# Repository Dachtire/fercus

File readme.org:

#+TITLE: Fercus
Wireless Symmetry Optical Keyboard[[./doc/image/overview.jpg]]

* Firmware
** Connect via RF 2.4GHz Proprietary, BLE 5.3, USB
** COMMENT optical switch with diff trigger mode
# - schmitt trigger
# - adc trigger
# - adc difference
** COMMENT function
# - multiple layers
# - repeat mode

* Hardware
** Switch
6*7 keys of each side, low profile optical switch
# - raesha low profile optical switch
# - keychron low profile optical switch
# - razer low profile optical switch

** Spec
Dimension: 133 * 137 * 14.35 mm

Weight of each side: 159 ± 1 g

power input: DC 5V 500mA

# current: 40 mA * 7 * 15 / 1000 = 4.2 mA

** response time
|    |       tr |       tf | unit |
| pt |       18 |        5 | us   |
# | sw | 200-2000 | 200-2000 | us   |
The speed of optical switch depends on the speed of finger, the shortest time for finger to press a switch is about 200 us, but usually it takes a few milliseconds.
Test on mcu's adc at f_adc = 12MHz, f_s = 12 / 14 MHz, resolution = 12 bits. Get the average of the five.

** COMMENT test
|    | min | typ | max | unit | cond                    |
| pt | 0.2 |     | 0.3 | V    | ir 20mA, without switch |

* Manual
** fn key
fn1: switch layout

fn2: switch connection mode. long press: rf Unbind with dongle

fn3: battery status

fn4: power on led green. power off led red.

** usb connection
- usb1 to connect with pc
#+begin_src org
              ┌────┐              
              │ pc │              
              └▲──▲┘              
               │  │               
    ┌───usb────┘  └────usb───┐    
    │                        │    
┌───▼──┬──────┐    ┌──────┬──▼───┐
│ usb1 │ usb2 │    │ usb2 │ usb1 │
├──────┴──────┤    ├──────┴──────┤
│    left     │    │    right    │
└─────────────┘    └─────────────┘
#+end_src
- usb2 to connect between left and right
#+begin_src org
              ┌────┐                                 ┌────┐              
              │ pc │                                 │ pc │              
              └▲───┘                                 └───▲┘              
               │                                         │               
    ┌───usb────┘                                         └────usb───┐    
    │                                                               │    
    │      ┌───usb────┐                           ┌───usb────┐      │    
    │      │          │                           │          │      │    
┌───▼──┬───▼──┐    ┌──▼───┬──────┐     ┌──────┬───▼──┐    ┌──▼───┬──▼───┐
│ usb1 │ usb2 │    │ usb2 │ usb1 │     │ usb1 │ usb2 │    │ usb2 │ usb1 │
├──────┴──────┤    ├──────┴──────┤     ├──────┴──────┤    ├──────┴──────┤
│    left     │    │    right    │     │    left     │    │    right    │
└─────────────┘    └─────────────┘     └─────────────┘    └─────────────┘
#+end_src

#               ┌────┐              
#               │ pc │              
#               └▲──▲┘              
#                │  │               
#     ┌───usb────┘  └────usb───┐    
#     │                        │    
#     │      ┌───usb────┐      │    
#     │      │          │      │    
# ┌───▼──┬───▼──┐    ┌──▼───┬──▼───┐
# │ usb1 │ usb2 │    │ usb2 │ usb1 │
# ├──────┴──────┤    ├──────┴──────┤
# │    left     │    │    right    │
# └─────────────┘    └─────────────┘

** RF connection
#+begin_src org
              ┌────┐              
              │ pc │              
              └─▲──┘              
                │usb              
             ┌──▼───┐             
  ┌─wireless─►dongle◄─wireless─┐  
  │          └──────┘          │  
  │                            │  
┌─▼───────────┐    ┌───────────▼─┐
│     RF      │    │     RF      │
├─────────────┤    ├─────────────┤
│    left     │    │    right    │
└─────────────┘    └─────────────┘
#+end_src

** BLE connection
#+begin_src org
              ┌────┐              
  ┌─wireless──► pc ◄──wireless─┐  
  │           └────┘           │  
  │                            │  
┌─▼───────────┐    ┌───────────▼─┐
│    BLE      │    │    BLE      │
├─────────────┤    ├─────────────┤
│    left     │    │    right    │
└─────────────┘    └─────────────┘
#+end_src

** mix connection
#+begin_src org
              ┌────┐              
              │ pc │              
              └▲───┘              
               │                  
    ┌───usb────┘                  
    │                             
    │      ┌─wireless─┐           
    │      │          │           
┌───▼──┬───▼──┐    ┌──▼───┬──────┐
│ usb1 │  RF  │    │  RF  │ usb1 │
├──────┴──────┤    ├──────┴──────┤
│    left     │    │    right    │
└─────────────┘    └─────────────┘
#+end_src

** power
auto power on/off when usb cable connected/disconnected

when idle for a week, first use fn4 to power off in firmware, then turn off hardware power switch

** layout
- qwerty[[./doc/keyboard-layout-editor/qwerty.png]]

* Assembly
** compoment
- pcb 1.6mm thickness
- plate 1.2mm thickness
- nut m2 length 2.5mm, od 3mm
- screw m2 length 4mm
- rubber 1mm thickness
- li-on battery 101550 800mAh, molex picoblade 3 pin, 8 cm cable length
- usb-c to usb-c cable 1 m
- usb-c to usb-a cable 2 m
  
** COMMENT PCBA
soldering nut on pcb, or soldering nut on plate

** Overall
1. Install switches on the plate, the LED position of the switch is facing upwards.
2. Install the plate to the PCB.[[./doc/image/assembly/assembly-1.jpg]]
3. Install the screws.[[./doc/image/assembly/assembly-2.jpg]]
4. Install keycaps.

* Thanks
[[https://discord.com/channels/715975244896272618][Optical Future Discord]]

* COMMENT FAQ
** COMMENT keys layout
*** thumb
finger splay increase the x axis distence between rows
more thumb keys may be hard to press
*** middle finger
[[./doc/keyboard-layout-editor/middle-finger.png]]
mid finger at wsad postion, non stagger is better to press up
bad for playing fps game
# same for pinky stagger 8 mm instand of 12 mm

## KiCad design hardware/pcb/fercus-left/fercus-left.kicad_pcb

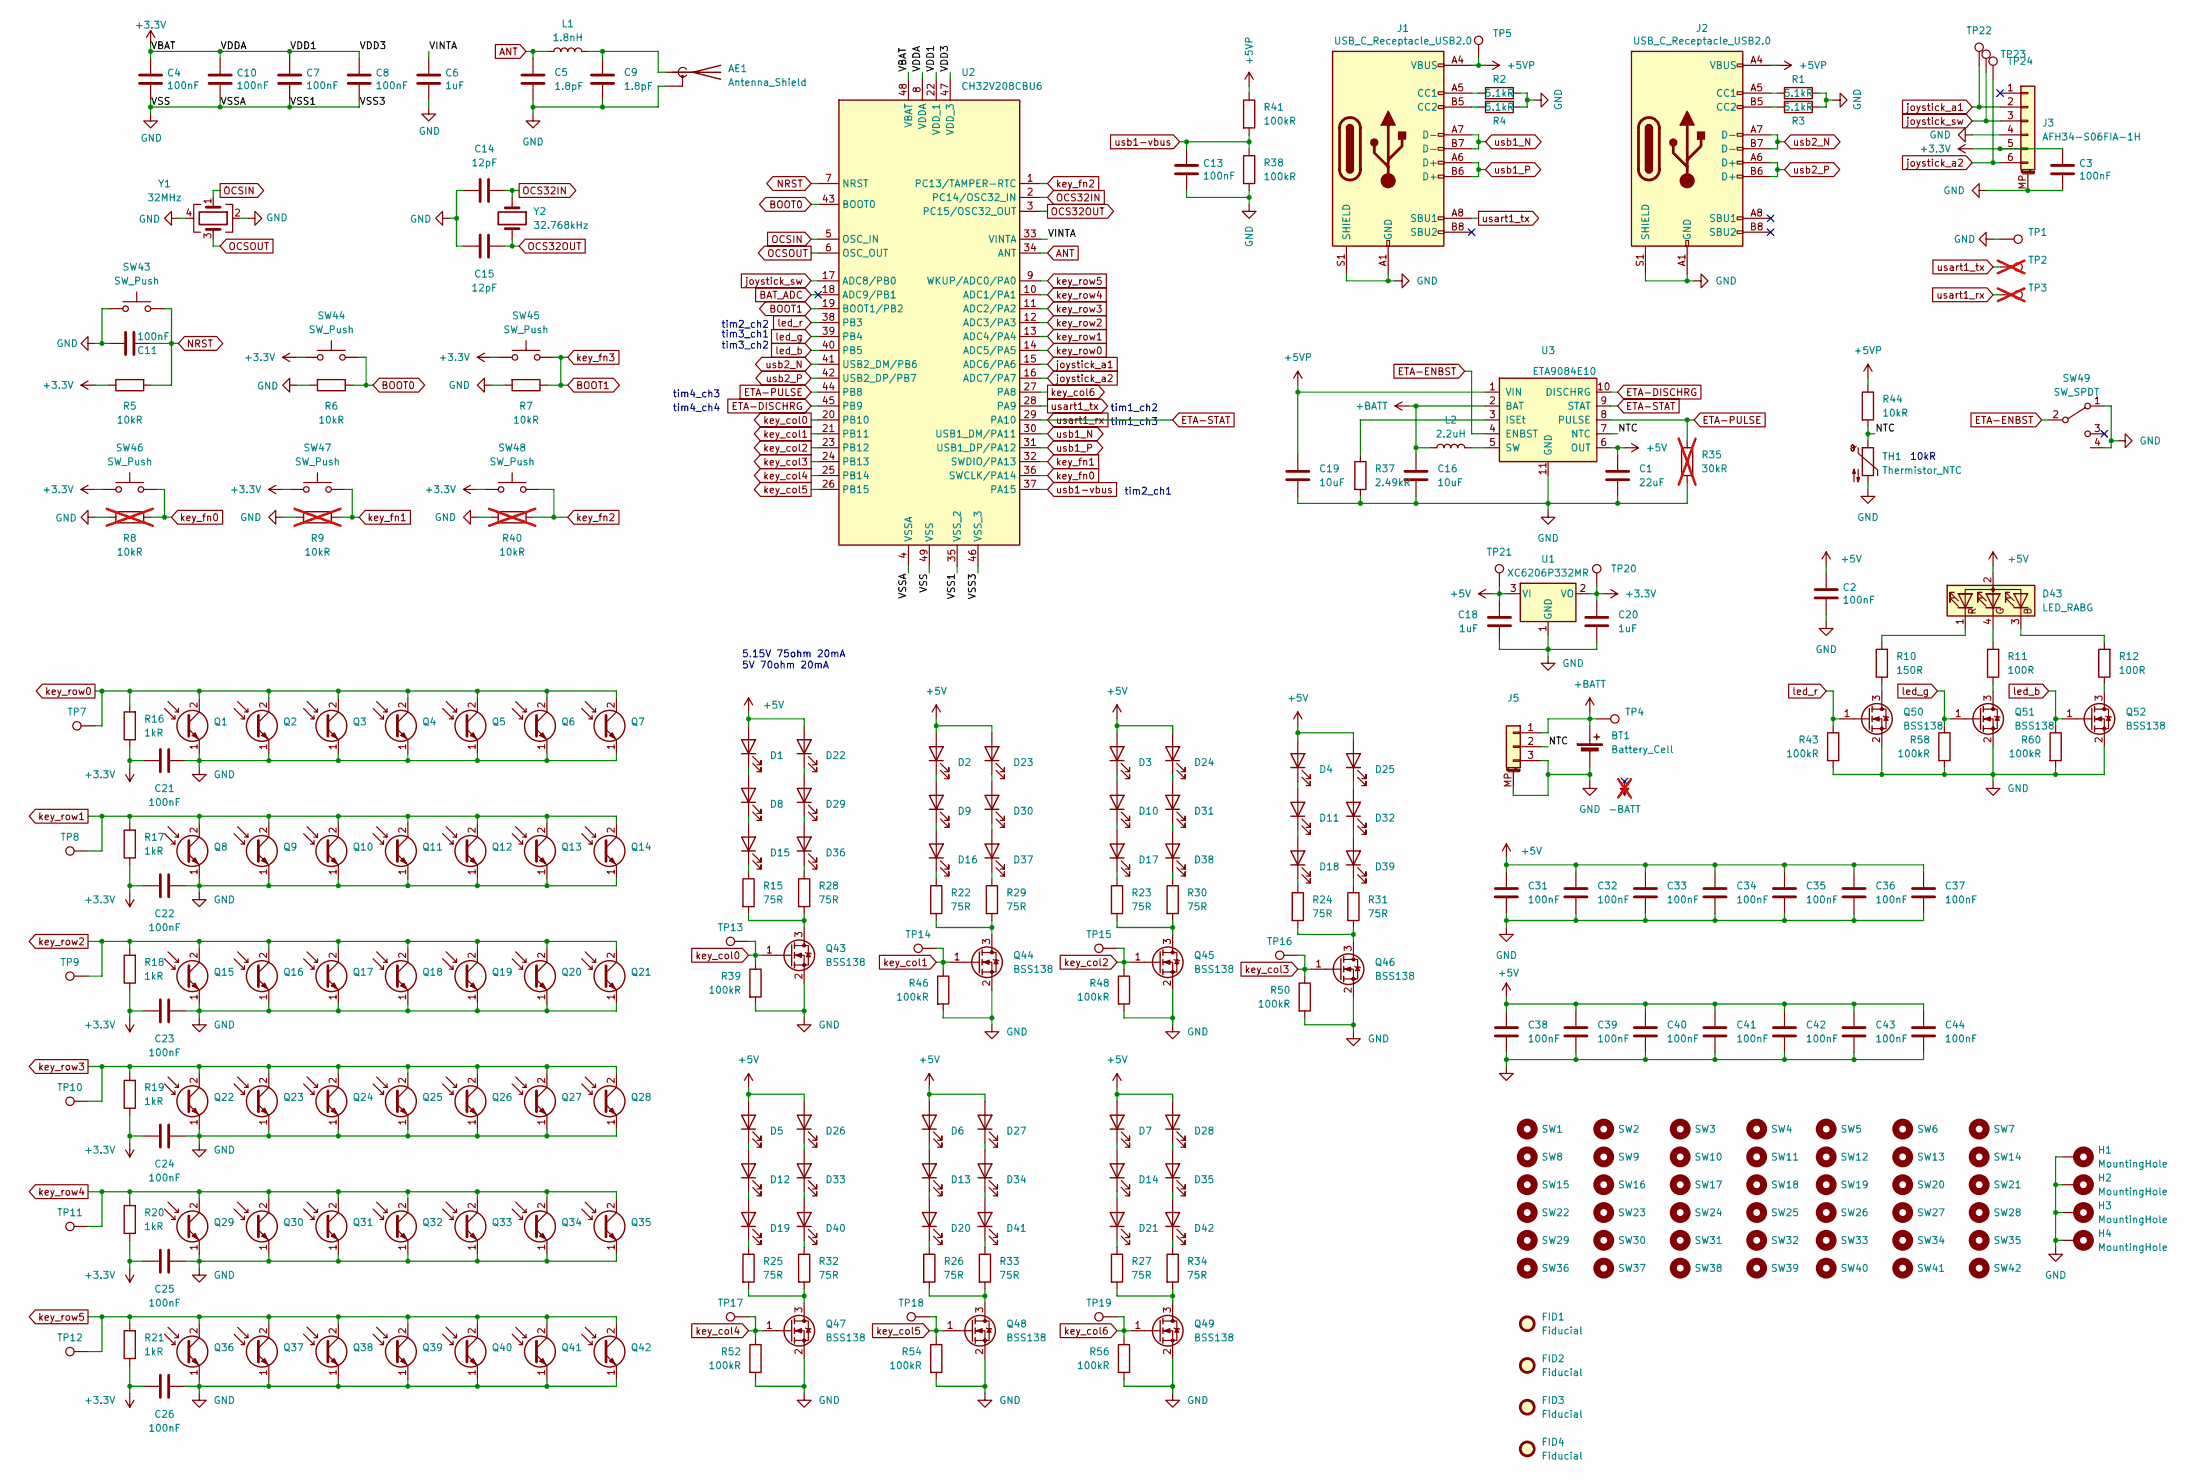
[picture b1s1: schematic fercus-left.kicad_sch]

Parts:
AE1: Antenna_Shield; WCH_MIFA-1_2.4G_1.6mm_FR4_Left_NoMask
BT1: Battery_Cell
C1: 22uF; C_0603_1608Metric
C2, C3, C4, C7, C8, C10, C11, C13, C21, C22, C23, C24, C25, C26, C31, C32, C33, C34, C35, C36, C37, C38, C39, C40, C41, C42, C43, C44: 100nF; C_0603_1608Metric
C5, C9: 1.8pF; C_0402_1005Metric
C6, C18, C20: 1uF; C_0603_1608Metric
C14, C15: 12pF; C_0402_1005Metric
C16: 10uF; C_0603_1608Metric
C19: 10uF; C_0805_2012Metric
D1, D2, D3, D4, D5, D6, D7, D8, D9, D10, D11, D12, D13, D14, D15, D16, D17, D18, D19, D20, D21, D22, D23, D24, D25, D26, D27, D28, D29, D30, D31, D32, D33, D34, D35, D36, D37, D38, D39, D40, D41, D42: KTR-0602IRC-850; KTR-0602IRC
D43: LED_RABG; Everlight_LED_RGB_PLCC-4
FID1, FID2, FID3, FID4: Fiducial; Fiducial_1mm_Mask3mm
H1, H2, H3, H4: MountingHole; MountingHole_2.2mm_M2_ISO14580_Pad
J1, J2: USB_C_Receptacle_USB2.0; USB_C_Receptacle_HRO_TYPE-C-31-M-12
J3: AFH34-S06FIA-1H; Jushuo_AFC42-S06FMA-1H_1x6-1MP_P0.50_Horizontal
J5: Molex_PicoBlade_53261-0371_1x03-1MP_P1.25mm_Horiz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; Molex_PicoBlade_53261-0371_1x03-1MP_P1.25mm_Horizontal
L1: 1.8nH; L_0402_1005Metric
L2: 2.2uH; L_Sunlord_MWSA0402S
Q1, Q2, Q3, Q4, Q5, Q6, Q7, Q8, Q9, Q10, Q11, Q12, Q13, Q14, Q15, Q16, Q17, Q18, Q19, Q20, Q21, Q22, Q23, Q24, Q25, Q26, Q27, Q28, Q29, Q30, Q31, Q32, Q33, Q34, Q35, Q36, Q37, Q38, Q39, Q40, Q41, Q42: KTR-0602PTD
Q43, Q44, Q45, Q46, Q47, Q48, Q49, Q50, Q51, Q52: BSS138; SOT-23
R1, R2, R3, R4: 5.1kR; R_0603_1608Metric
R5, R6, R7, R44: 10kR; R_0603_1608Metric
R8, R9, R40: 10kR; R_0603_1608Metric; not fitted
R10: 150R; R_0603_1608Metric
R11, R12: 100R; R_0603_1608Metric
R15, R22, R23, R24, R25, R26, R27, R28, R29, R30, R31, R32, R33, R34: 75R; R_0603_1608Metric
R16, R17, R18, R19, R20, R21: 1kR; R_0603_1608Metric
R35: 30kR; R_0603_1608Metric; not fitted
R37: 2.49kR; R_0402_1005Metric
R38, R39, R41, R43, R46, R48, R50, R52, R54, R56, R58, R60: 100kR; R_0603_1608Metric
SW1, SW2, SW3, SW4, SW5, SW6, SW7, SW8, SW9, SW10, SW11, SW12, SW13, SW14, SW15, SW16, SW17, SW18, SW19, SW20, SW21, SW22, SW23, SW24, SW25, SW26, SW27, SW28, SW29, SW30, SW31, SW32, SW33, SW34, SW35, SW36, SW37, SW38, SW39, SW40, SW41, SW42: SW_Optical; SW_RAESHA_Low_Profile_Optical
SW43, SW44, SW45, SW46, SW47, SW48: SW_Push; SW_SPST_TL3342
SW49: SW_SPDT; SW_SPDT_PCM12
TH1: Thermistor_NTC; R_0603_1608Metric
TP1, TP4, TP5, TP7, TP8, TP9, TP10, TP11, TP12, TP13, TP14, TP15, TP16, TP17, TP18, TP19, TP20, TP21, TP22, TP23, TP24: TestPoint; TestPoint_Pad_D1.0mm
TP2, TP3: TestPoint; TestPoint_Pad_D1.0mm; not fitted
U1: XC6206P332MR; SOT-23-3
U2: CH32V208CBU6; QFN-48-1EP_5x5mm_P0.35mm_EP3.7x3.7mm_ThermalVias_Drill0.3mm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
U3: ETA9084E10; SSOP-10-1EP_3.9x4.9mm_P1.00mm_EP2.4x2.8mm_ThermalVias_Drill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
Y1: 32MHz; Crystal_SMD_3225-4Pin_3.2x2.5mm
Y2: 32.768kHz; Crystal_SMD_3215-2Pin_3.2x1.5mm

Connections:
+3.3V: C3.1, C4.1, C7.1, C8.1, C10.1, C20.1, C21.1, C22.1, C23.1, C24.1, C25.1, C26.1, J3.5, R5.1, R16.1, R17.1, R18.1, R19.1, R20.1, R21.1, SW44.1, SW45.1, SW46.1, SW47.1, SW48.1, TP20.1, U1.2 (VO), U2.8 (VDDA), U2.22 (VDD_1), U2.47 (VDD_3), U2.48 (VBAT)
+5V: C1.1, C2.1, C18.1, C31.2, C32.2, C33.2, C34.2, C35.2, C36.2, C37.2, C38.2, C39.2, C40.2, C41.2, C42.2, C43.2, C44.2, D1.2 (A), D2.2 (A), D3.2 (A), D4.2 (A), D5.2 (A), D6.2 (A), D7.2 (A), D22.2 (A), D23.2 (A), D24.2 (A), D25.2 (A), D26.2 (A), D27.2 (A), D28.2 (A), D43.2 (A), TP21.1, U1.3 (VI), U3.6 (OUT)
+5VP: C19.1, J1.A4 (VBUS), J1.A9 (VBUS), J1.B4 (VBUS), J1.B9 (VBUS), J2.A4 (VBUS), J2.A9 (VBUS), J2.B4 (VBUS), J2.B9 (VBUS), R41.1, R44.1, TP5.1, U3.1 (VIN)
+BATT: BT1.1 (+), C16.1, J5.1, L2.1, TP4.1, U3.2 (BAT)
/NTC: J5.2, R44.2, TH1.1, U3.7 (NTC)
/VINTA: C6.1, U2.33 (VINTA)
ANT: C5.1, L1.1, U2.34 (ANT)
BAT_ADC: U2.18 (ADC9/PB1)
BOOT0: R6.1, SW44.2, U2.43 (BOOT0)
BOOT1: R7.1, SW45.2, U2.19 (BOOT1/PB2)
ETA-DISCHRG: U2.45 (PB9), U3.10 (DISCHRG)
ETA-ENBST: SW49.2 (B), U3.4 (ENBST)
ETA-PULSE: R35.1, U2.44 (PB8), U3.8 (PULSE)
ETA-STAT: TP3.1, U2.29 (PA10), U3.9 (STAT)
GND: AE1.2 (Shield), BT1.2 (-), C1.2, C2.2, C3.2, C4.2, C5.2, C6.2, C7.2, C8.2, C9.2, C10.2, C11.2, C13.2, C14.2, C15.2, C16.2, C18.2, C19.2, C20.2, C21.2, C22.2, C23.2, C24.2, C25.2, C26.2, C31.1, C32.1, C33.1, C34.1, C35.1, C36.1, C37.1, C38.1, C39.1, C40.1, C41.1, C42.1, C43.1, C44.1, H1.1, H2.1, H3.1, H4.1, J1.A1 (GND), J1.A12 (GND), J1.B1 (GND), J1.B12 (GND), J1.S1 (SHIELD), J2.A1 (GND), J2.A12 (GND), J2.B1 (GND), J2.B12 (GND), J2.S1 (SHIELD), J3.4, J3.MP (MountPin), J5.3, J5.MP (MountPin), Q1.1 (E), Q2.1 (E), Q3.1 (E), Q4.1 (E), Q5.1 (E), Q6.1 (E), Q7.1 (E), Q8.1 (E), Q9.1 (E), Q10.1 (E), Q11.1 (E), Q12.1 (E), Q13.1 (E), Q14.1 (E), Q15.1 (E), Q16.1 (E), Q17.1 (E), Q18.1 (E), Q19.1 (E), Q20.1 (E), Q21.1 (E), Q22.1 (E), Q23.1 (E), Q24.1 (E), Q25.1 (E), Q26.1 (E), Q27.1 (E), Q28.1 (E), Q29.1 (E), Q30.1 (E), Q31.1 (E), Q32.1 (E), Q33.1 (E), Q34.1 (E), Q35.1 (E), Q36.1 (E), Q37.1 (E), Q38.1 (E), Q39.1 (E), Q40.1 (E), Q41.1 (E), Q42.1 (E), Q43.2 (S), Q44.2 (S), Q45.2 (S), Q46.2 (S), Q47.2 (S), Q48.2 (S), Q49.2 (S), Q50.2 (S), Q51.2 (S), Q52.2 (S), R1.1, R2.1, R3.1, R4.1, R6.2, R7.2, R8.2, R9.2, R35.2, R37.2, R38.2, R39.2, R40.2, R43.2, R46.2, R48.2, R50.2, R52.2, R54.2, R56.2, R58.2, R60.2, SW43.1, SW49.1 (A), SW49.4, TH1.2, TP1.1, U1.1 (GND), U2.4 (VSSA), U2.35 (VSS_2), U2.46 (VSS_3), U2.49 (VSS), U3.11 (GND), Y1.2, Y1.4
NRST: C11.1, R5.2, SW43.2, U2.7 (NRST)
unnamed: AE1.1 (A), C9.1, L1.2
unnamed: D1.1 (K), D8.2 (A)
unnamed: D2.1 (K), D9.2 (A)
unnamed: D3.1 (K), D10.2 (A)
unnamed: D10.1 (K), D17.2 (A)
unnamed: D4.1 (K), D11.2 (A)
unnamed: D11.1 (K), D18.2 (A)
unnamed: D5.1 (K), D12.2 (A)
unnamed: D12.1 (K), D19.2 (A)
unnamed: D6.1 (K), D13.2 (A)
unnamed: D13.1 (K), D20.2 (A)
unnamed: D7.1 (K), D14.2 (A)
unnamed: D14.1 (K), D21.2 (A)
unnamed: D8.1 (K), D15.2 (A)
unnamed: D15.1 (K), R15.1
unnamed: D9.1 (K), D16.2 (A)
unnamed: D16.1 (K), R22.1
unnamed: D17.1 (K), R23.1
unnamed: D18.1 (K), R24.1
unnamed: D19.1 (K), R25.1
unnamed: D20.1 (K), R26.1
unnamed: D21.1 (K), R27.1
unnamed: D22.1 (K), D29.2 (A)
unnamed: D23.1 (K), D30.2 (A)
unnamed: D24.1 (K), D31.2 (A)
unnamed: D25.1 (K), D32.2 (A)
unnamed: D26.1 (K), D33.2 (A)
unnamed: D27.1 (K), D34.2 (A)
unnamed: D28.1 (K), D35.2 (A)
unnamed: D29.1 (K), D36.2 (A)
unnamed: D30.1 (K), D37.2 (A)
unnamed: D31.1 (K), D38.2 (A)
unnamed: D32.1 (K), D39.2 (A)
unnamed: D33.1 (K), D40.2 (A)
unnamed: D34.1 (K), D41.2 (A)
unnamed: D35.1 (K), D42.2 (A)
unnamed: D36.1 (K), R28.1
unnamed: D37.1 (K), R29.1
unnamed: D38.1 (K), R30.1
unnamed: D39.1 (K), R31.1
unnamed: D40.1 (K), R32.1
unnamed: D41.1 (K), R33.1
unnamed: D42.1 (K), R34.1
unnamed: D43.3 (BK), R12.2
unnamed: D43.4 (GK), R11.2
unnamed: D43.1 (RK), R10.2
unnamed: J1.A5 (CC1), R2.2
unnamed: J1.B5 (CC2), R4.2
unnamed: J2.A5 (CC1), R1.2
unnamed: J2.B5 (CC2), R3.2
unnamed: Q43.3 (D), R15.2, R28.2
unnamed: Q44.3 (D), R22.2, R29.2
unnamed: Q45.3 (D), R23.2, R30.2
unnamed: Q46.3 (D), R24.2, R31.2
unnamed: Q47.3 (D), R25.2, R32.2
unnamed: Q48.3 (D), R26.2, R33.2
unnamed: Q49.3 (D), R27.2, R34.2
unnamed: Q50.3 (D), R10.1
unnamed: Q51.3 (D), R11.1
unnamed: Q52.3 (D), R12.1
unnamed: R37.1, U3.3 (ISEt)
unnamed: L2.2, U3.5 (SW)
OCS32IN: C14.1, U2.2 (PC14/OSC32_IN), Y2.1
OCS32OUT: C15.1, U2.3 (PC15/OSC32_OUT), Y2.2
OCSIN: U2.5 (OSC_IN), Y1.1
OCSOUT: U2.6 (OSC_OUT), Y1.3
joystick_a1: J3.2, TP22.1, U2.15 (ADC6/PA6)
joystick_a2: J3.6, TP24.1, U2.16 (ADC7/PA7)
joystick_sw: J3.3, TP23.1, U2.17 (ADC8/PB0)
key_col0: Q43.1 (G), R39.1, TP13.1, U2.20 (PB10)
key_col1: Q44.1 (G), R46.1, TP14.1, U2.21 (PB11)
key_col2: Q45.1 (G), R48.1, TP15.1, U2.23 (PB12)
key_col3: Q46.1 (G), R50.1, TP16.1, U2.24 (PB13)
key_col4: Q47.1 (G), R52.1, TP17.1, U2.25 (PB14)
key_col5: Q48.1 (G), R54.1, TP18.1, U2.26 (PB15)
key_col6: Q49.1 (G), R56.1, TP19.1, U2.27 (PA8)
key_fn0: R8.1, SW46.2, U2.36 (SWCLK/PA14)
key_fn1: R9.1, SW47.2, U2.32 (SWDIO/PA13)
key_fn2: R40.1, SW48.2, U2.1 (PC13/TAMPER-RTC)
key_row0: Q1.2 (C), Q2.2 (C), Q3.2 (C), Q4.2 (C), Q5.2 (C), Q6.2 (C), Q7.2 (C), R16.2, TP7.1, U2.14 (ADC5/PA5)
key_row1: Q8.2 (C), Q9.2 (C), Q10.2 (C), Q11.2 (C), Q12.2 (C), Q13.2 (C), Q14.2 (C), R17.2, TP8.1, U2.13 (ADC4/PA4)
key_row2: Q15.2 (C), Q16.2 (C), Q17.2 (C), Q18.2 (C), Q19.2 (C), Q20.2 (C), Q21.2 (C), R18.2, TP9.1, U2.12 (ADC3/PA3)
key_row3: Q22.2 (C), Q23.2 (C), Q24.2 (C), Q25.2 (C), Q26.2 (C), Q27.2 (C), Q28.2 (C), R19.2, TP10.1, U2.11 (ADC2/PA2)
key_row4: Q29.2 (C), Q30.2 (C), Q31.2 (C), Q32.2 (C), Q33.2 (C), Q34.2 (C), Q35.2 (C), R20.2, TP11.1, U2.10 (ADC1/PA1)
key_row5: Q36.2 (C), Q37.2 (C), Q38.2 (C), Q39.2 (C), Q40.2 (C), Q41.2 (C), Q42.2 (C), R21.2, TP12.1, U2.9 (WKUP/ADC0/PA0)
led_b: Q52.1 (G), R60.1, U2.40 (PB5)
led_g: Q51.1 (G), R58.1, U2.39 (PB4)
led_r: Q50.1 (G), R43.1, U2.38 (PB3)
usart1_tx: J1.A8 (SBU1), TP2.1, U2.28 (PA9)
usb1-vbus: C13.1, R38.1, R41.2, U2.37 (PA15)
usb1_N: J1.A7 (D-), J1.B7 (D-), U2.30 (USB1_DM/PA11)
usb1_P: J1.A6 (D+), J1.B6 (D+), U2.31 (USB1_DP/PA12)
usb2_N: J2.A7 (D-), J2.B7 (D-), U2.41 (USB2_DM/PB6)
usb2_P: J2.A6 (D+), J2.B6 (D+), U2.42 (USB2_DP/PB7)

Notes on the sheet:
tim4_ch4
tim1_ch3
tim2_ch2
10kR
5.15V 75ohm 20mA 5V 70ohm 20mA
tim2_ch1
tim4_ch3
tim1_ch2
tim3_ch2
tim3_ch1

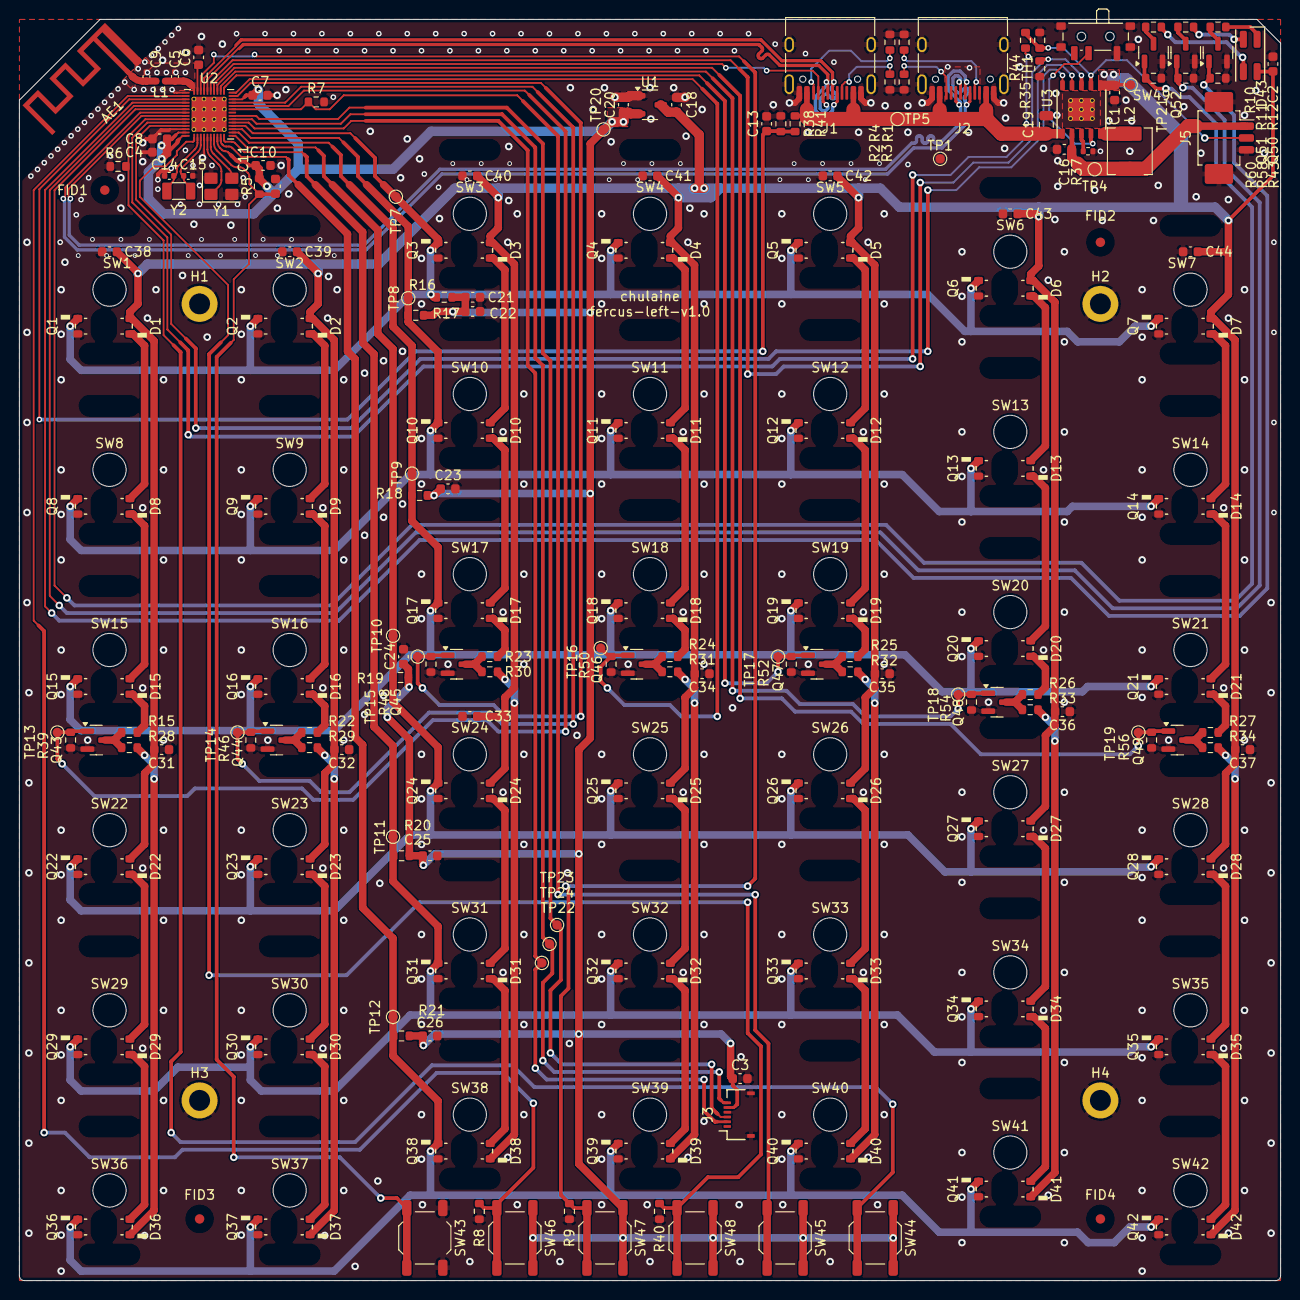
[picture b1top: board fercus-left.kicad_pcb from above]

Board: 2 copper layers, 133.0 x 133.0 mm, 272 parts (0 on the bottom side), 109 nets.

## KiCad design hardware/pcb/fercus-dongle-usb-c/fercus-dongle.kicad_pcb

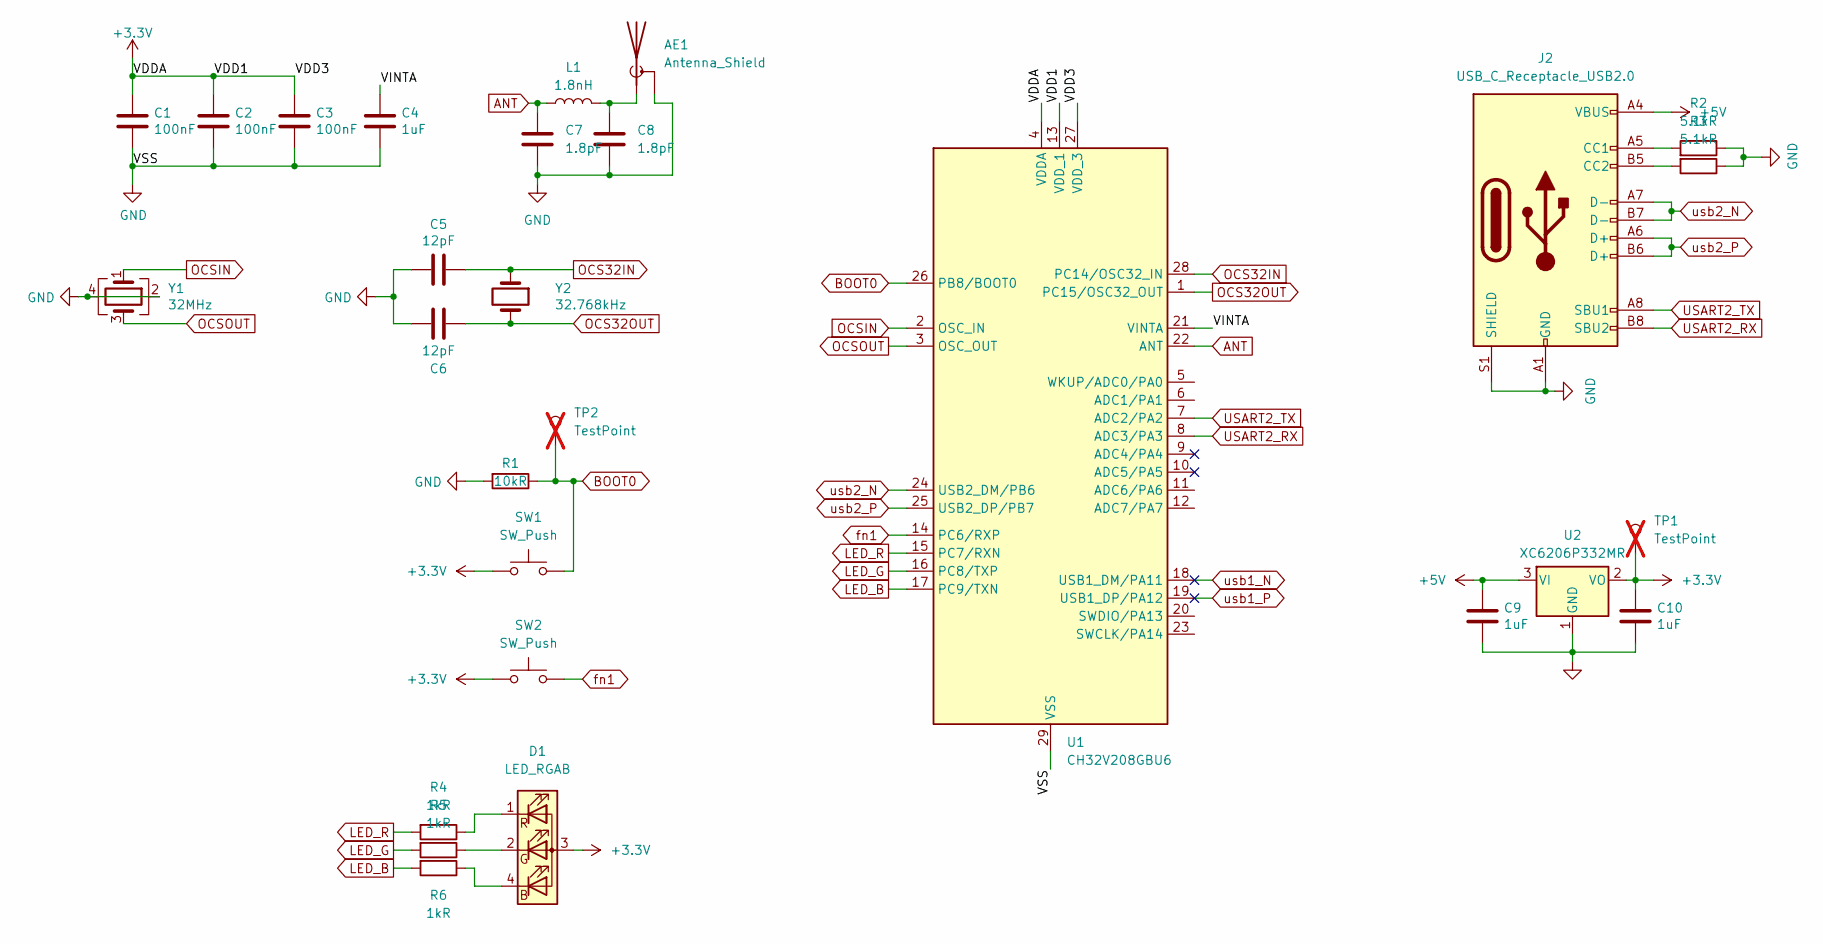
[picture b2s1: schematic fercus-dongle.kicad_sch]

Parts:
AE1: Antenna_Shield; WCH_MIFA-1_2.4GHz_1.6mm_FR4_Left_Mask
C1, C2, C3: 100nF; C_0402_1005Metric
C4, C9, C10: 1uF; C_0402_1005Metric
C5, C6: 12pF; C_0402_1005Metric
C7, C8: 1.8pF; C_0402_1005Metric
D1: LED_RGAB; KTR-B1615RGBC+
J2: USB_C_Receptacle_USB2.0; USB_C_Receptacle_HRO_TYPE-C-31-M-12
L1: 1.8nH; L_0402_1005Metric
R1: 10kR; R_0402_1005Metric
R2, R3: 5.1kR; R_0402_1005Metric
R4, R5, R6: 1kR; R_0402_1005Metric
SW1, SW2: SW_Push; SW_SPST_CK_KXT3
TP1, TP2: TestPoint; TestPoint_Pad_D1.0mm; not fitted
U1: CH32V208GBU6; QFN-28-1EP_4x4mm_P0.4mm_EP2.6x2.6mm_ThermalVias_Drill0.3mm
U2: XC6206P332MR; SOT-23
Y1: 32MHz; Crystal_SMD_2016-4Pin_2.0x1.6mm
Y2: 32.768kHz; Crystal_SMD_2012-2Pin_2.0x1.2mm

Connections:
+3.3V: C1.1, C2.1, C3.1, C10.1, D1.3 (A), SW1.1, SW2.1, TP1.1, U1.4 (VDDA), U1.13 (VDD_1), U1.27 (VDD_3), U2.2 (VO)
+5V: C9.1, J2.A4 (VBUS), J2.A9 (VBUS), J2.B4 (VBUS), J2.B9 (VBUS), U2.3 (VI)
/VINTA: C4.1, U1.21 (VINTA)
ANT: C7.1, L1.1, U1.22 (ANT)
BOOT0: R1.1, SW1.2, TP2.1, U1.26 (PB8/BOOT0)
GND: AE1.2 (Shield), C1.2, C2.2, C3.2, C4.2, C5.2, C6.2, C7.2, C8.2, C9.2, C10.2, J2.A1 (GND), J2.A12 (GND), J2.B1 (GND), J2.B12 (GND), J2.S1 (SHIELD), R1.2, R2.1, R3.1, U1.29 (VSS), U2.1 (GND), Y1.2, Y1.4
LED_B: R6.2, U1.17 (PC9/TXN)
LED_G: R5.2, U1.16 (PC8/TXP)
LED_R: R4.2, U1.15 (PC7/RXN)
unnamed: AE1.1 (A), C8.1, L1.2
unnamed: D1.4 (BK), R6.1
unnamed: D1.2 (GK), R5.1
unnamed: D1.1 (RK), R4.1
unnamed: J2.A5 (CC1), R2.2
unnamed: J2.B5 (CC2), R3.2
OCS32IN: C5.1, U1.28 (PC14/OSC32_IN), Y2.1
OCS32OUT: C6.1, U1.1 (PC15/OSC32_OUT), Y2.2
OCSIN: U1.2 (OSC_IN), Y1.1
OCSOUT: U1.3 (OSC_OUT), Y1.3
USART2_RX: J2.B8 (SBU2), U1.8 (ADC3/PA3)
USART2_TX: J2.A8 (SBU1), U1.7 (ADC2/PA2)
fn1: SW2.2, U1.14 (PC6/RXP)
usb1_N: U1.18 (USB1_DM/PA11)
usb1_P: U1.19 (USB1_DP/PA12)
usb2_N: J2.A7 (D-), J2.B7 (D-), U1.24 (USB2_DM/PB6)
usb2_P: J2.A6 (D+), J2.B6 (D+), U1.25 (USB2_DP/PB7)

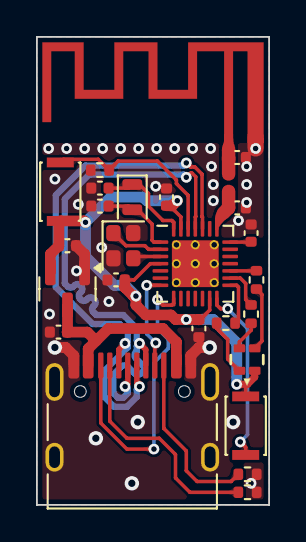
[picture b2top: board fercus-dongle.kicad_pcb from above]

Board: 2 copper layers, 12.9 x 26.0 mm, 26 parts (0 on the bottom side), 24 nets.

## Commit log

2022-07-23 v0.3.0
    add (firmware):
    system: 24Mhz HXTAL for 96Mhz system clock
    usb: hid keyborad
    feat (keyboard):
    uart dma communication
    multiple layers
2022-12-14 doc: add readme, license, image
2022-12-14 fw/ch32v: disable DEBUG_UART1
2022-12-14 fw/ch32v/usbd: add ONE_DESCRIPTOR
2022-12-14 fw/ch32v/usbd: add ENDP_ADDR
2022-12-14 fw/gd32v/usbfs: add device class, config
2022-12-14 fw/gd32v/usbfs: add usb hid define, usage
2022-12-14 fw: add keyboard
2022-12-14 fw/ch32v: rename usbd_composite_km to app
2022-12-14 fw/ch32v/usbd: merge 'v1.6' CH32V20xEVT/EXAM/USB/USBD/CompositeKM/User/USBLIB
    rename USBLIB to usbd
    rename CONFIG to config
    rename USB-Driver to driver
2022-12-14 fw/ch32v: add keyboard init to main()
2022-12-14 fw/ch32v: add define HSE_VALUE 24Mhz
2022-12-14 fw/gd32v/usbfs: merge GD32VF103_Firmware_Library_V1.1.4/Firmware/GD32VF103_usbfs_library/driver/Include
2022-12-14 fw/ch32v: add gpio_config(), USART1_Init(), TIM1_Init(), DMA_Tx_Init(), ADC_Function_Init(), USB_Sleep_Wakeup_CFG()
2022-12-14 fw/ch32v/usbd: add ENDP_SIZE
2022-12-14 fw/ch32v: add TIM1_UP_IRQHandler()
2022-12-14 fw/gd32v/usbfs: merge GD32VF103_Firmware_Library_V1.1.4/Firmware/GD32VF103_usbfs_library/ustd/common
2022-12-14 fw/ch32v/usbd: add EP1_OUT_Callback(), EP2_OUT_Callback()
2022-12-14 fw/ch32v: add 24Mhz HSE in SetSysClockTo144_HSE()
2022-12-14 fw/gd32v/usbfs: add USB_CLASS_VENDOR
2022-12-14 fw/makefile: add
2022-12-14 fw/ch32v: merge 'v1.6' CH32V20xEVT/EXAM/USB/USBD/CompositeKM/User
2022-12-14 fw/ch32v: merge 'v1.6' CH32V20xEVT/EXAM/SRC
2022-12-14 hw/pcb: add
2022-12-14 hw/case: add
2022-12-14 fw/gd32v/usbfs: merge GD32VF103_Firmware_Library_V1.1.4/Firmware/GD32VF103_usbfs_library/ustd/class/hid
    rename GD32VF103_usbfs_library to usbfs
2022-12-14 fw/ch32v: remove duplicate TIM3_Init(), TIM3_IRQHandler()
2022-12-14 fw/ch32v/usbfs: merge 'v1.6' CH32V20xEVT/EXAM/USB/USBFS/HOST_KM/User/USB_Host
2022-12-14 hw/plate: add
2022-12-14 fw: change gpio pin
2022-12-14 fw/ch32v/usbfs: remove duplicate USBFS_RCC_Init()
2022-12-14 fw/ch32v/usbfs: merge 'v1.6' CH32V20xEVT/EXAM/USB/USBFS/DEVICE/CompositeKM/User
2022-12-14 fw: add keyboard adc diff mode
    rename kb_adc_init() in keyboard.c to adc_config() in app.c
2022-12-14 fw: add kb_adc_time()
2022-12-14 hw/case: add joystick
2022-12-14 fw: add kb_adc_test3()
2022-12-14 Revert "fw/ch32v: disable DEBUG_UART1"
    This reverts commit 79287d2343aa877df28748973e31bd921e492df9.
2022-12-14 fw: add keyboard adc trigger mode
2022-12-14 fw/ch32v: add rcc adc clock
2022-12-14 fw: remove kb_adc_test()
2022-12-14 fw/usbfs: add usb host hid keyboard
    add usbh_epin_time() from TIM3_IRQHandler(), replace TIM3 with TIM1
2022-12-14 fw/ch32v: add usbh init to main()
2022-12-14 fw/ch32v: add usbfs host data handle, usbfs host init to main()
2022-12-14 fw/ch32v/usbfs: add include
2022-12-14 fw: remove printf in kb_usbhd_combine()
2022-12-14 hw/pcb: remove led
2022-12-14 doc: fix readme style
2022-12-15 doc/image: update overview
2022-12-15 hw/plate: remove led
2022-12-15 hw: change joystick mounting hole d
2022-12-15 fw/gd32v/usbfs: rename cntlr desc
2022-12-15 fw/gd32v/usbfs: rename paraments of usb_hid_desc_config_set
2022-12-15 fw/js: add gpio define, init, adc dma
2022-12-15 fw: fix define array size
2022-12-15 fw/ch32v/usbd: add USBD_COMPOSITE ONE_DESCRIPTOR
2022-12-15 fw/gd32v/usbfs: fix usbd_composite class
2022-12-16 doc: update usb connection
2022-12-16 fw/gd32v/usbfs: add usbd_cntlr_report_send()
2022-12-20 fw: fix cntlr handler
2022-12-20 doc: update time desc
2022-12-20 fw: fix kb handler
2022-12-28 fw: fix define
2022-12-28 fw: fix usb_prop
2024-04-20 init
    hw: add
    fw: add
    doc: add
2024-06-08 merge
    fw:
    - fix usb product string, vid
    - add rf_phy_hop
    - add RF_BondingErase()
    - change default layout key fn to pause
    - fix power manager poweroff when usb disconnect
2024-09-21 merge
    hw:
    - fix sch
    - fix plate
    - rename to fercus-dongle-usb-a
    doc:
    - add assembly
2025-12-21 hw: add footprint library
